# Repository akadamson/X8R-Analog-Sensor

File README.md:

X8R-Analog-Sensor
=================

Analog Sensor for the Frsky X8R receiver and it's S-Port

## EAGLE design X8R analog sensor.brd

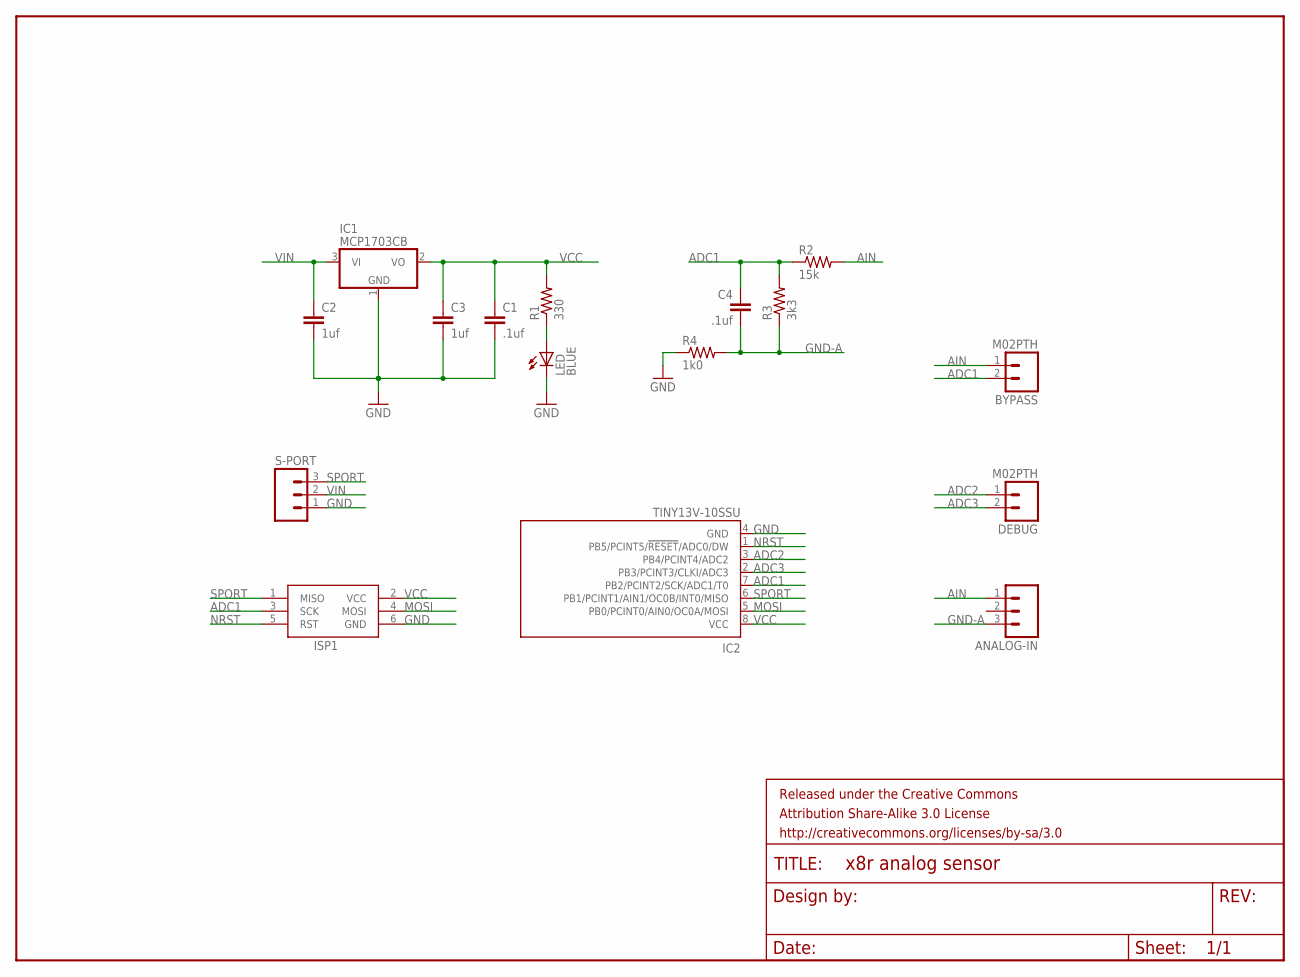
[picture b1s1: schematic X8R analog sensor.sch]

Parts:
ANALOG-IN: M03PTH; 1X03
BYPASS: M02PTH; 1X02
C1, C4: .1uf; 0603-CAP
C2, C3: 1uf; 0603-CAP
DEBUG: M02PTH; 1X02
FRAME1: FRAME-LETTER; CREATIVE_COMMONS
IC1: MCP1703CB; SOT23
IC2: TINY13V-10SSU; 8S1
ISP1: AVRISP-6; AVRISP
LED: BLUE; LED-0603
R1: 330; 0603-RES
R2: 15k; 0603-RES
R3: 3k3; 0603-RES
R4: 1k0; 0603-RES
S-PORT: M03PTH; 1X03

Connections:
ADC1: BYPASS.2, C4.1, IC2.7 (PB2/PCINT2/SCK/ADC1/T0), ISP1.3 (SCK), R2.1, R3.2
ADC2: DEBUG.1, IC2.3 (PB4/PCINT4/ADC2)
ADC3: DEBUG.2, IC2.2 (PB3/PCINT3/CLKI/ADC3)
AIN: ANALOG-IN.1, BYPASS.1, R2.2
GND: C1.2, C2.2, C3.2, IC1.1 (GND), IC2.4 (GND), ISP1.6 (GND), LED.C, R4.1, S-PORT.1
GND-A: ANALOG-IN.3, C4.2, R3.1, R4.2
MOSI: IC2.5 (PB0/PCINT0/AIN0/OC0A/MOSI), ISP1.4 (MOSI)
unnamed: LED.A, R1.1
NRST: IC2.1 (PB5/PCINT5/!RESET!/ADC0/DW), ISP1.5 (RST)
SPORT: IC2.6 (PB1/PCINT1/AIN1/OC0B/INT0/MISO), ISP1.1 (MISO), S-PORT.3
VCC: C1.1, C3.1, IC1.2 (VO), IC2.8 (VCC), ISP1.2 (VCC), R1.2
VIN: C2.1, IC1.3 (VI), S-PORT.2

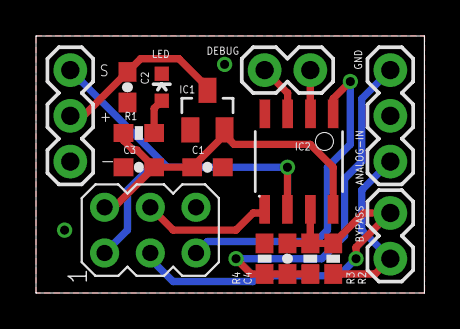
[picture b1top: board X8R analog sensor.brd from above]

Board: 2 copper layers, 21.6 x 14.3 mm, 17 parts (0 on the bottom side), 12 nets.

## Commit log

2013-10-22 added eagle files
2013-10-23 updated for voltage divider, and ISP interface
2013-10-23 fixed silkscreen issue on bottom of board
2013-10-23 updated bypass caps as tantalums aren't needed
2013-10-23 updated for a bypass cap on the AIN side, and changed the 3 pin connector for AIN to a 2 pin
2013-10-23 added OSHPARK gerbers in zip file
2013-10-23 reverted back to the 3 pin connector on AIN
2013-10-24 small non-functional tweaks to the board layout, updated gerbers
2014-03-02 updated v2 version with separate grounds
2014-03-02 updated for actual version
2014-03-02 added pdf of schematic
2014-03-19 updated git with gerbers
2014-03-19 updated with GPL License
2014-03-19 updated with gerber files
2014-03-19 removed wrong gerber file

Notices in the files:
parts and their libraries:
SparkFun-Capacitors: Licensing: CC v3.0 Share-Alike You are welcome to use this library for commercial purposes.
SparkFun-Aesthetics: Released under the Creative Commons Attribution Share-Alike 3.0 License
SparkFun-Aesthetics: http://creativecommons.org/licenses/by-sa/3.0
